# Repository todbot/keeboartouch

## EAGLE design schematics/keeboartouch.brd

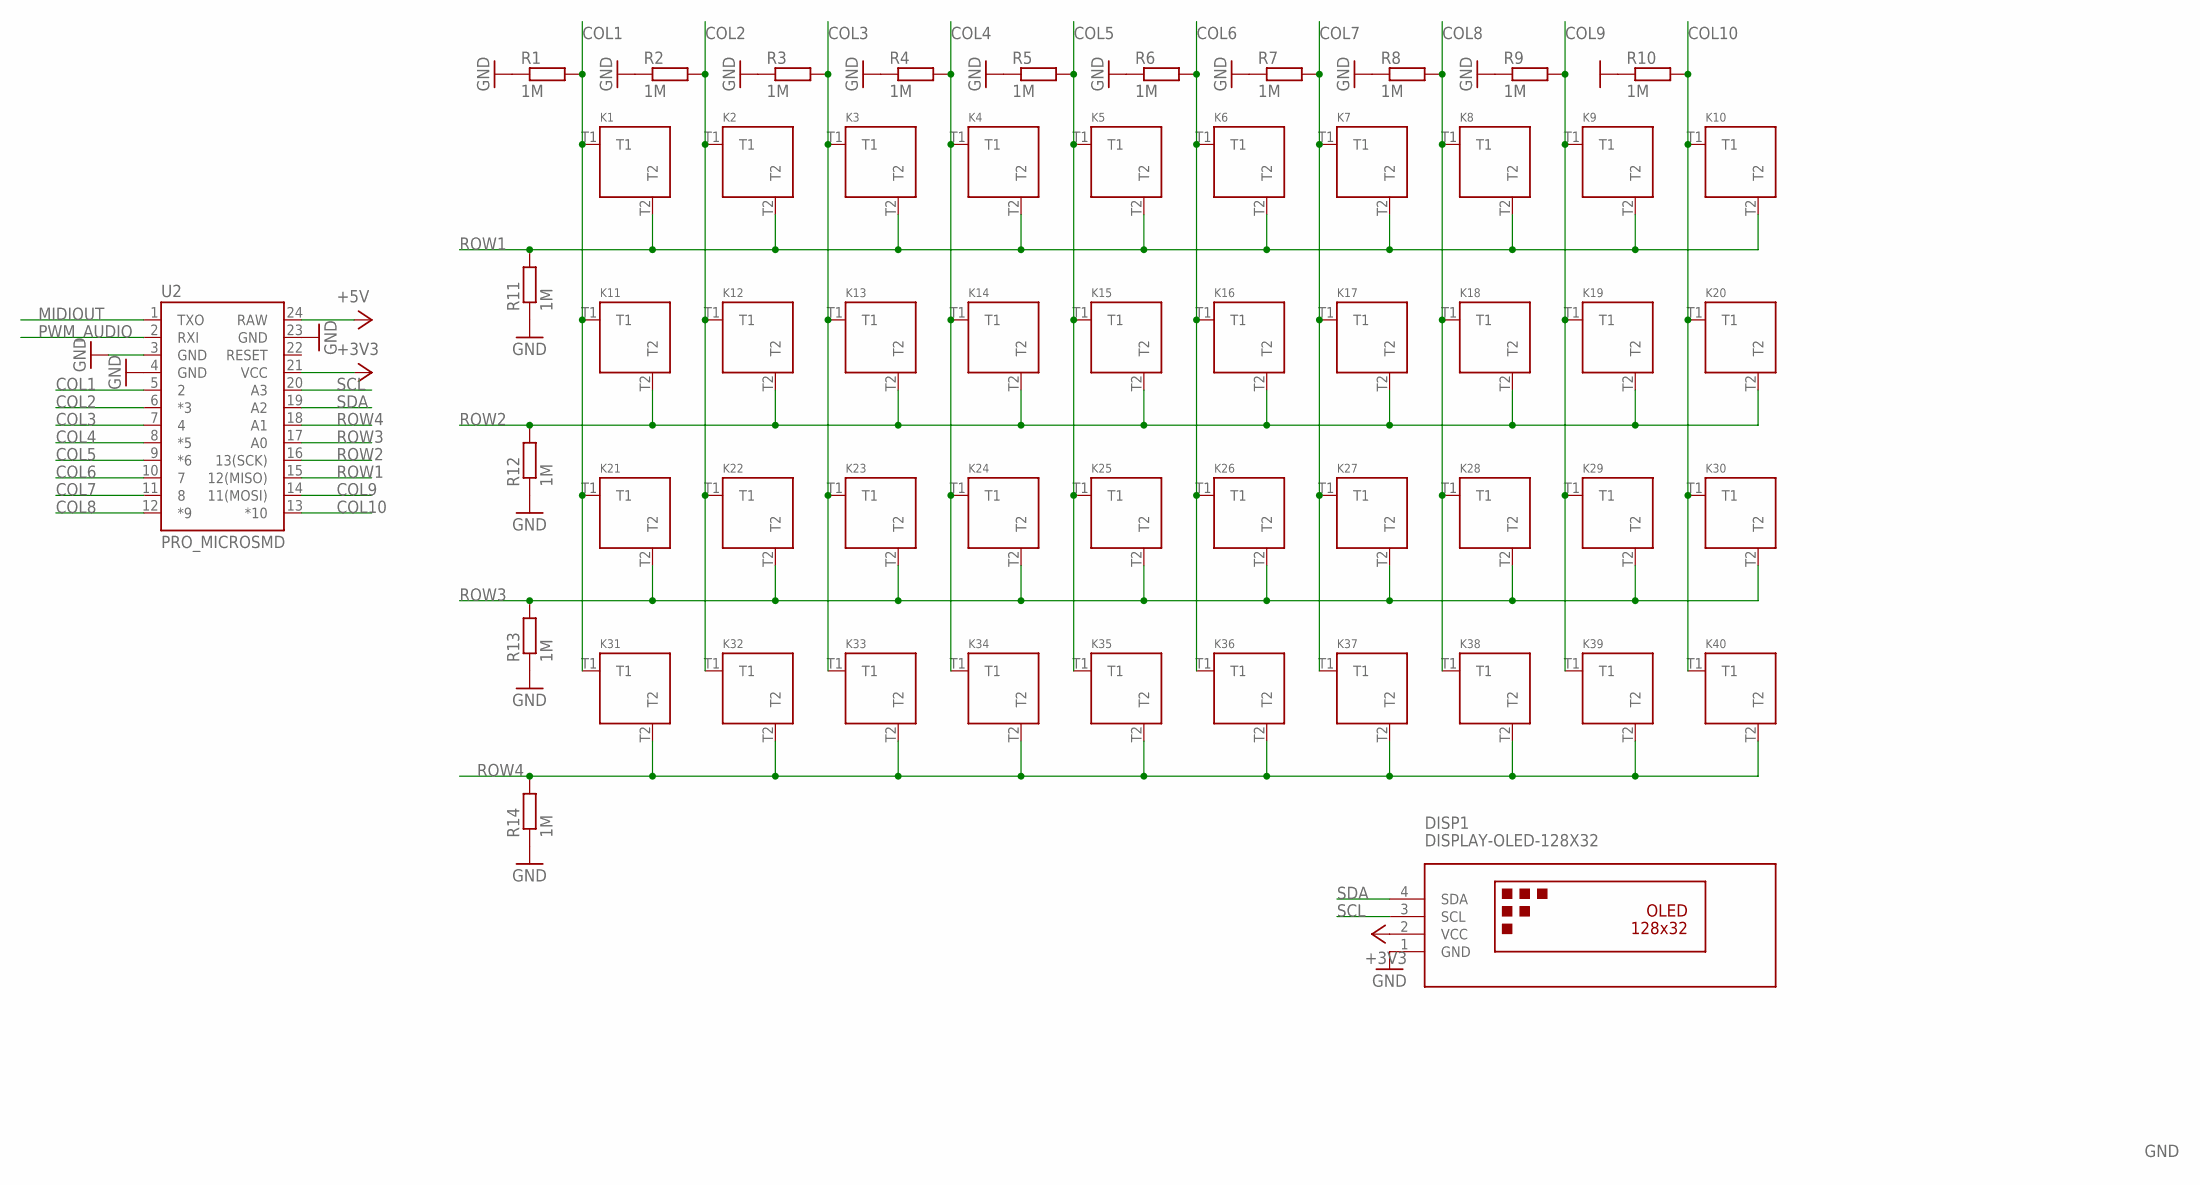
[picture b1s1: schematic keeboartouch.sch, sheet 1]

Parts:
DISP1: DISPLAY-OLED-128X32
K1, K2, K3, K4, K5, K6, K7, K8, K9, K10, K11, K12, K13, K14, K15, K16, K17, K18, K19, K20, K21, K22, K23, K24, K25, K26, K27, K28, K29, K30, K31, K32, K33, K34, K35, K36, K37, K38, K39, K40: TOUCHKEY; TOUCHPAD_KEY_0.5IN
R1, R2, R3, R4, R5, R6, R7, R8, R9, R10, R11, R12, R13, R14: 1M; R0805
U2: PRO_MICROSMD; PRO_MICRO_SMD

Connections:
+3V3: DISP1.2 (VCC), U2.21 (VCC)
+5V: U2.24 (RAW)
COL1: K1.T1, K11.T1, K21.T1, K31.T1, R1.2, U2.5 (2)
COL2: K2.T1, K12.T1, K22.T1, K32.T1, R2.2, U2.6 (*3)
COL3: K3.T1, K13.T1, K23.T1, K33.T1, R3.2, U2.7 (4)
COL4: K4.T1, K14.T1, K24.T1, K34.T1, R4.2, U2.8 (*5)
COL5: K5.T1, K15.T1, K25.T1, K35.T1, R5.2, U2.9 (*6)
COL6: K6.T1, K16.T1, K26.T1, K36.T1, R6.2, U2.10 (7)
COL7: K7.T1, K17.T1, K27.T1, K37.T1, R7.2, U2.11 (8)
COL8: K8.T1, K18.T1, K28.T1, K38.T1, R8.2, U2.12 (*9)
COL9: K9.T1, K19.T1, K29.T1, K39.T1, R9.2, U2.14 (11(MOSI))
COL10: K10.T1, K20.T1, K30.T1, K40.T1, R10.2, U2.13 (*10)
GND: DISP1.1 (GND), R1.1, R2.1, R3.1, R4.1, R5.1, R6.1, R7.1, R8.1, R9.1, R10.1, R11.1, R12.1, R13.1, R14.1, U2.3 (GND), U2.4 (GND), U2.23 (GND)
MIDIOUT: U2.1 (TXO)
PWM_AUDIO: U2.2 (RXI)
ROW1: K1.T2, K2.T2, K3.T2, K4.T2, K5.T2, K6.T2, K7.T2, K8.T2, K9.T2, K10.T2, R11.2, U2.15 (12(MISO))
ROW2: K11.T2, K12.T2, K13.T2, K14.T2, K15.T2, K16.T2, K17.T2, K18.T2, K19.T2, K20.T2, R12.2, U2.16 (13(SCK))
ROW3: K21.T2, K22.T2, K23.T2, K24.T2, K25.T2, K26.T2, K27.T2, K28.T2, K29.T2, K30.T2, R13.2, U2.17 (A0)
ROW4: K31.T2, K32.T2, K33.T2, K34.T2, K35.T2, K36.T2, K37.T2, K38.T2, K39.T2, K40.T2, R14.2, U2.18 (A1)
SCL: DISP1.3 (SCL), U2.20 (A3)
SDA: DISP1.4 (SDA), U2.19 (A2)

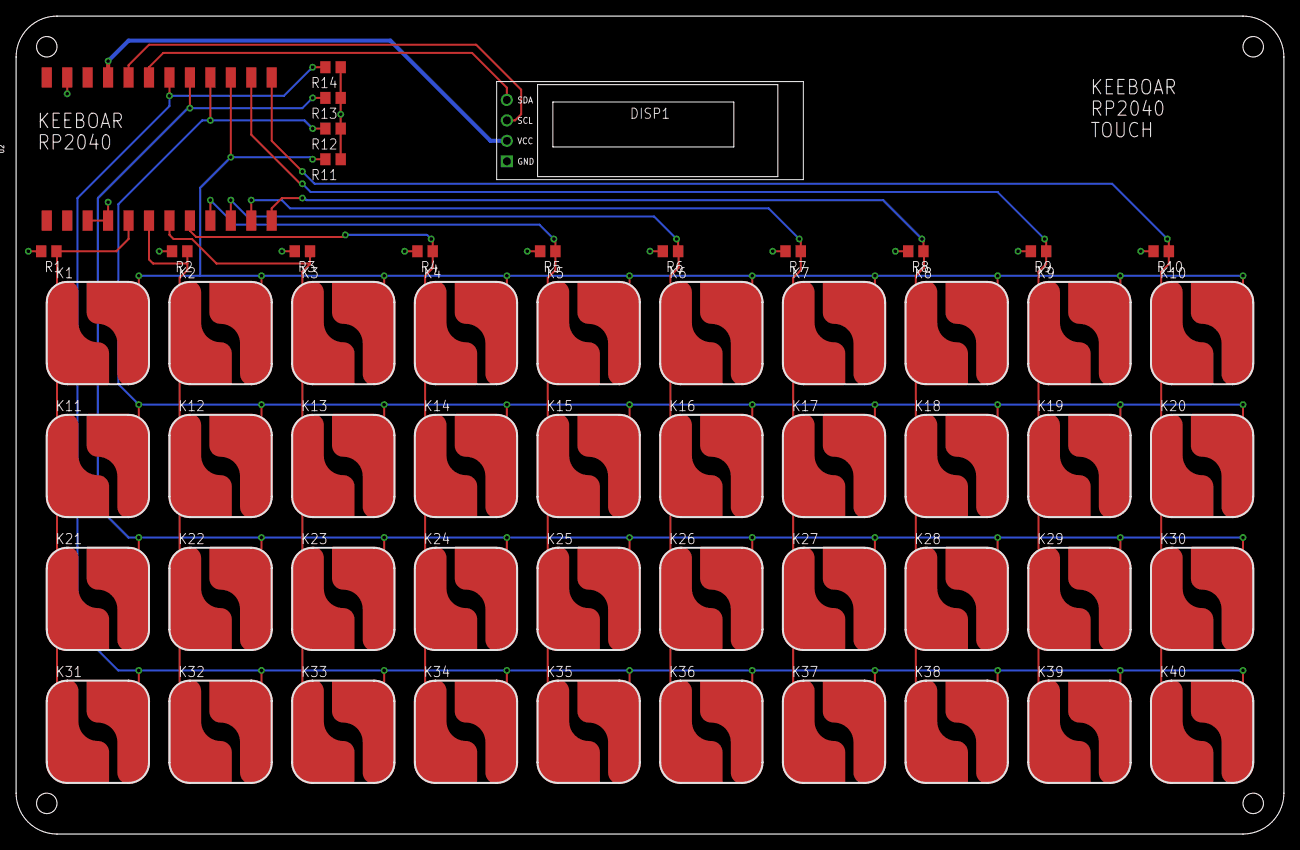
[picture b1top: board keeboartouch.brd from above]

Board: 2 copper layers, 157.5 x 101.6 mm, 56 parts (0 on the bottom side), 18 nets.

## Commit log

2023-01-30 first sch brd commit
2023-01-30 four mount holes thx to jp
2023-01-31 now with silly topsilk

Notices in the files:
parts and their libraries:
diy-modules: Released under the Creative Commons Attribution 4.0 International License: http://creativecommons.org/licenses/by/4.0
